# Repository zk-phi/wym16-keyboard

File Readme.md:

# wym16 Keyboard

パーツの組み付け順を変えることで、１台で様々なケース構成方法（プレートの固定方式）を試せるお得なキーパッドです。

組み立てた後でも、同じトッププレートを使用する固定方法についてはハンダを剥がすことなく行き来することができます。

高級志向になりつつある自作/カスタムキーボードでケースの構成方法は重要になってくるトピックの一つだと思いますが、スイッチなどと違って「とりあえずいろんな種類を買ってみて比較する」というのもなかなか難しいので設計してみました。

ケースの形状、キーのレイアウト、ケース全体の質量などほぼすべての条件が同一の状態で色々な固定方式を試せるため、方式ごとの純粋な特徴を観察することができると期待しています。打面の高さもどの方式で組んでもぴったり同じになるようにしてあります。

自分のお気に入りのケースのタイプを見つける参考になればいいなと思います。

## 作れる構成

トッププレートなしで組めるもの

- トレイマウント (プレートレス)

トッププレート小を使用するもの

- トレイマウント (プレートあり)
- ボトムマウント
- トップマウント
- ガスケットマウント (要ガスケット)

トッププレート大を使用するもの

- サンドイッチマウント

同じトッププレートを使用する構成であれば、組み立てた後でもハンダを剥がすことなく行き来できるようになっています。

また「トレイマウント」系以外は、タイピングできる必要がないのであれば基板をハンダせずにスイッチテスターのように組み立てることもできます。

### 基板を固定する方式
#### ケースマウント (プレートなし / あり)

基板をケースに固定し、スイッチプレートは浮かせておく方式です。

プレートはあってもなくても組むことができます (これも打鍵感に影響するとされます)。

### プレートを固定する方式

プレートをケースに固定し、基板は吊り下げておく方式です。

プレートの固定方法によってさらに分類があります。

プレート自体は通常のものと、スロットの入ったリーフスプリングマウント風のもの (おためし) から選べます。

#### ボトムマウント

ケースの下側にプレートを固定する方式です。

#### トップマウント

ケースの上側にプレートを固定する方式です。

#### ガスケットマウント

ゴムなど柔らかめの素材でプレートを上下から柔らかく挟み込む方式です。

#### サンドイッチマウント

ケースの上側と下側でプレートをがっちり挟み込む方式です。

## 必要なパーツ

- キット
  - プレート (10 種 12 枚)
  - 基板
  - (おまけ リーフスプリング風？トッププレート x1)

- 電子部品
  - MX 互換スイッチ x16
  - ダイオード 1N4148w x16
  - Pro Micro

- ケース部品
  - M2 ネジ
    - 6mm x 4 (プレートマウント用)
    - 8mm x 4 (ケースマウント用)
    - 21mm x 4 ~ 9
      - キャスト材の場合は 20mm でもいいかも
  - M2 ナット
    - 型問わず x 13
    - 三種 x 8 (ケースマウント時のスペーサ用)
      - 三種＝少し薄手の (1.2mm) ナット
  - 2mm 厚ゴム板 (ガスケットマウント用)
  - ゴム足 x4

## プレートの命名

プレートの形状が 10 種類 (おまけ込み 11 種類) もあってヤバいので、組立ガイドでは以下の名前で呼ぶことにします。

### ボトムプレート

一種類しかないので一番わかりやすいです。いつでも底板として使用します。

### トッププレート

スイッチの穴がたくさん空いているプレートがトッププレートです。

大きい方はサンドイッチマウント専用で、それ以外の方式ではすべて小さい方を使います。

おまけで小さい方のプレートに切れ込みを入れたものも作ってみました。

ネジ穴周辺の強度をあえて落とすことでしなりを均一にする効果を期待しています (リーフマウント方式ということもあるみたいです) が、アクリルでどれくらいちゃんと機能するかは未知数です。

### トップフレーム

残りの外枠フレームたちのうち、 *MicroUSB の差し込み口が開いていない* ものを「トップフレーム」と呼ぶことにします。

これらはすべてトッププレートより上側に使用します。

- 普通のトップフレーム

一番穴の少ないシンプルな形のものです。 3mm と 2mm の２種類の厚みがあります。

3mm のものは全ての固定方法で一番上に重ねて使用する化粧板です。

2mm のものはほとんどの構成で化粧板の下に敷いて使用しますが、「トップマウント」時には代わりに「ネジ穴付きトップフレーム」を使用します。

- ネジ穴付きトップフレーム

ネジ穴が４つ多く開いているトップフレームです。

「トップマウント」時にトッププレートを固定するための穴になっています。他の固定方法では使用しません。

- タブ穴付きトップフレーム

小さい方のトッププレートが収まりそうな、変な形の穴があいたトップフレームです。

3mm と 2mm の２種類の厚みがあり、 3mm の方には四隅に小さな出っ張りのようなものがついています。

3mm のものは、トッププレート (小) を使用するすべての固定方法でトッププレートを囲うための外枠として使用します (ちょうどトッププレートも 3mm です)。

2mm のものは主にトッププレートの上に使用します。

### ミドルフレーム

残りの外枠フレームたちには、 *MicroUSB の差し込み口が開いてい* ます。これらを「ミドルフレーム」と呼ぶことにします。

これらはすべてトッププレートより下側に使用します。

- 普通のミドルフレーム

一番穴の少ないシンプルな形のものです。 3mm と 2mm の２種類の厚みがあります。

3mm のものは全ての構成方法でボトムプレートのすぐ上に載せて使用します。

2mm のものはほとんどの構成でその上に載せて使用しますが、「ボトムマウント」時には代わりに「ネジ穴付きミドルフレーム」を使用します。

- ネジ穴付きミドルフレーム

ネジ穴が４つ多く開いているミドルフレームです。

「ボトムマウント」時にトッププレートを固定するために使用します。他の固定方法では使用しません。

- タブ穴付きミドルフレーム

一番複雑な形状をしたフレームです。割れやすいので注意してください。

主にトッププレートの下に使用します。

## 基板の組立て

キー入力をできるようにしたい場合、あるいはケースマウントを試したい場合、ハンダ付けが必須です。

### ProMicro にファームウェアを書き込んでおく

ProMicro にあらかじめファームウェアを書き込んでおきます。

https://github.com/zk-phi/keyboard-buildguide-common/blob/master/firmware.markdown

[こちら](https://github.com/zk-phi/qmk_firmware) にファームウェアをアップロードしておきます。

```
make handwired/wym16:default:avrdude
```

### ProMicro にコンスルーを実装しておく

ProMicro を基板に連結するためのコンスルーを実装します。

https://github.com/zk-phi/keyboard-buildguide-common/blob/master/conthrough.markdown

このキーボードでは ProMicro を「部品面が内側になるように」使用します。

### ダイオードを実装

https://github.com/zk-phi/keyboard-buildguide-common/blob/master/diode.markdown

### スイッチを実装

最後にスイッチを実装します。

試したいマウント方法にあったトッププレートを使用してください。

ProMicro の真裏にくるスイッチの足は ProMicro の個体によっては干渉するので、あらかじめ切っておくのがおすすめです。

https://github.com/zk-phi/keyboard-buildguide-common/blob/master/switch.markdown

## ケースの組立 / ケースマウント

使用しないプレート：トッププレート (大)、ネジ穴付きトップフレーム、ネジ穴付きミドルフレーム

1. ボトムプレートにミドルフレーム 3mm/2mm を重ね、その上にタブ穴付きミドルフレームを載せる

トッププレートが下にたわむ余地を残した方が公平に比較できるので、タブ穴付きを一番上にしています。

2. 基板の４つの足にナットを 2 つづつ履かせて、ボトムプレートにネジで取り付ける

ナットが１個 1.2mm なので、２個重ねることで基板がボトムプレートから 2.4mm 浮いた状態になります。

他のマウント方法と打面の高さをぴったり揃うので、公平に比較できます。

3. タブ穴付きトップフレーム 3mm, 2mm、トップフレーム 2mm, 3mm をこの順に載せて、全体をネジで締めて完成

## ケースの組立 / ボトムマウント

使用しないプレート：トッププレート (大)、ネジ穴付きトップフレーム、普通のミドルフレーム

使用するトッププレート：小さい方

1. トッププレートの下にネジ穴付きミドルフレームを敷き、ネジで固定する

2. ボトムプレートにミドルフレーム 3mm、タブ穴付きミドルフレームをこの順に重ね、上に 1. を載せる

3. タブ穴付きトップフレーム 3mm, 2mm、トップフレーム 2mm, 3mm をこの順に載せて、全体をネジで締めて完成

## ケースの組立 / トップマウント

使用しないプレート：トッププレート (大)、普通のトップフレーム、ネジ穴付きミドルフレーム

1. タブ穴付きトップフレーム 3mm にトッププレートをはめ、上にネジ穴付きトップフレームを載せ、ネジで固定する

2. ボトムプレートにミドルフレーム 3mm, 2mm、タブ穴付きミドルフレームをこの順に重ね、上に 1. を載せる

3. タブ穴付きトップフレーム 2mm, トップフレーム 3mm をこの順に重ねて、全体をネジで締めて完成

## ケースの組立 / ガスケットマウント

使用しないプレート：トッププレート (大)、ネジ穴付きトップフレーム、ネジ穴付きミドルフレーム

1. ボトムプレートの上にミドルフレーム 3mm, 2mm、タブ付きミドルフレームをこの順に重ねる

3. 2mm 厚のゴム板をカットして、４つのタブ穴に仕込む

4. 基板＆トッププレートを載せる

5. タブ付きトップフレーム 3mm, 2mm をこの順に重ねる

6. 2mm 厚のゴム板をカットして、４つのタブ穴に仕込む

7. トップフレーム 2mm, 3mm を載せて、全体をネジで締めて完成

## ケースの組立 / サンドイッチマウント

使用しないプレート：トッププレート (小)、ネジ穴付きトップフレーム、ネジ穴付きミドルフレーム

1. ボトムプレートの上にミドルフレーム 3mm, 2mm、タブ付きミドルフレームをこの順に重ねる

2. 基板＆大きなトッププレートを載せる

3. タブ付きトップフレーム 2mm、 トップフレーム 2mm, 3mm をこの順に重ねて、全体をネジで締めて完成

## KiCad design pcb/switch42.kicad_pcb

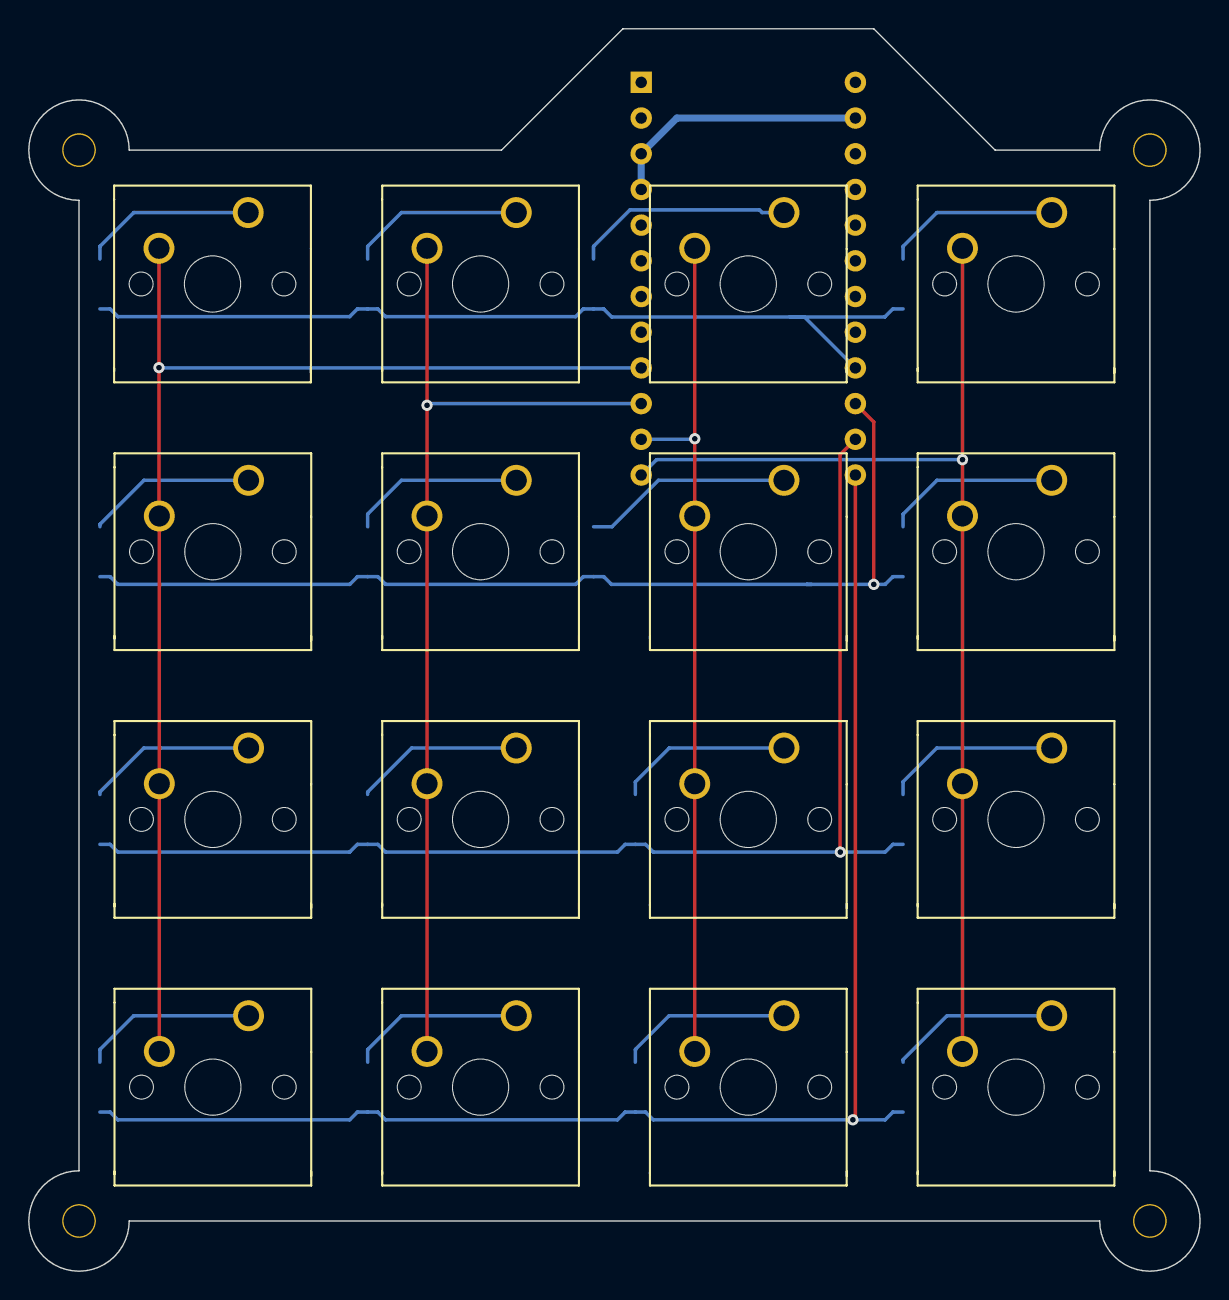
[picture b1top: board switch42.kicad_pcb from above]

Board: 2 copper layers, 83.3 x 88.4 mm, 37 parts (1 on the bottom side), 25 nets.

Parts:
D1, D2, D3, D4, D5, D6, D7, D8, D9, D10, D11, D12, D13, D14, D15, D16: D; D_SMD-irreversible
Ref**: Val**; M2_SCREW_HOLE_Plated
Ref**#2, Ref**#3, Ref**#4: Val**; M2_SCREW_HOLE_Plated
SW1, SW2, SW3, SW4, SW5, SW6, SW7, SW8, SW9, SW10, SW11, SW12, SW13, SW14, SW15, SW16: SW_PUSH; MX_1.00u-irreversible
U1: ProMicro; ProMicro_Reversed_Conthrough-irreversible

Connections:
GND: U1.3, U1.4, U1.23
unnamed: D1.2, SW1.2
unnamed: D2.2, SW2.2
unnamed: D3.2, SW3.2
unnamed: D4.2, SW4.2
unnamed: D5.2, SW5.2
unnamed: D6.2, SW6.2
unnamed: D7.2, SW7.2
unnamed: D8.2, SW8.2
unnamed: D9.2, SW9.2
unnamed: D10.2, SW10.2
unnamed: D11.2, SW11.2
unnamed: D12.2, SW12.2
unnamed: D13.2, SW13.2
unnamed: D14.2, SW14.2
unnamed: D15.2, SW15.2
unnamed: D16.2, SW16.2
col0: SW1.1, SW2.1, SW3.1, SW4.1, U1.9
col1: SW5.1, SW6.1, SW7.1, SW8.1, U1.10
col2: SW9.1, SW10.1, SW11.1, SW12.1, U1.11
col3: SW13.1, SW14.1, SW15.1, SW16.1, U1.12
row0: D1.1, D5.1, D9.1, D13.1, U1.16
row1: D2.1, D6.1, D10.1, D14.1, U1.15
row2: D3.1, D7.1, D11.1, D15.1, U1.14
row3: D4.1, D8.1, D12.1, D16.1, U1.13

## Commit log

2020-08-27 Add/rename images
2020-08-27 Beautify link
2020-08-27 Fix link syntax
2020-08-27 Update animations
2020-08-27 Fix readme
2020-08-30 Update buildguide
